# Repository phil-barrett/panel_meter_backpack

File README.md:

# Panel Meter Backpacks

Those cheap Chinese panel ammeters and voltmeters are nice additions to a project but often require some convoluted wiring. In addition, it appears that people are easily confused about the connections, the number of complaints about poor instructions and dead meters seem to indicate that.

I have been using them for a number of projects and evolved designs to make them easier to use. The AHA! moment came when I realized I could clip a PCB onto the back of the meter.  They all seem to use exactly the same plastic bezel so I could standardize the openings in the PCB.

# 5 digit USB Ammeter Ver 2.21

I was building a test setup for my [Teensy 4.1 CNC Breakout Board](https://github.com/phil-barrett/grblHAL-teensy-4.x/blob/master/README.md) and wanted to monitor USB current. The Teensy 4.1 is fairly power hungry and my board pulls even more.  I wanted to know what kind of burden the setup was placing on the USB output of my PC. In addition, I wanted to be able to characterize current draw based on various features in use.

While I had a decent DMM with fairly accurate current measuring capability, I wanted something a bit more permanant without a lot of extra wires.  The ammeter I settled on is a generic "5 digit" panel meter that sells for $6-10 USD from the usual suspect sources. I paid about $13 with tax and shipping. Characterizing it, I found it was surprisingly good, within 100 microAmps of my DMM. I designed the back pack with USB A and microUSB recepticles. It connects in-line and doesn't adversely affect USB communication. USB powers the meter itself.

My first PCB had a couple of small errors but was functional. Here is Version 2.21.
 
Here is the updated version 2.30 installed on the Panel Meter.

And, finally, mounted on a temporary panel. The light you see at the top and bottom of the meter face is light shining through from the back. It does not show when mounted in the panel of an enclosed box. 

The second iteration fixed a dumb footprint problem and used differential routing for the USB data lines. I also added silk screened information to make it clear which wires connect where. [Kicad files are here](https://github.com/phil-barrett/panel_ammeter_backpack/tree/main/design_files). However, this uses a microUSB connector I found on eBay a couple of years ago. A quick check did not show anything availble from the same source. It probably isn't available anywhere else.  I am looking for a suitable DigiKey/Mouser sourced part and will post Kicad files and an OSHPark shared project link. 

## Update

I received the V2.30 boards back from OSHPark and they work great! See the USB Ammeter V2.30 section below.

# Ammeter/Voltmeter Ver 2.50

I liked the design so much, I designed another one for those ubiquitous volt and current panel meters you see all over the place. This one uses a barrel jack and/or a screw terminal for 5-24 Volts. The meter can be powered from 5V to 30V and measure up to 100V.  I have it set up to power the meter from the measured voltage.  If you want to measure more than 30V, you will need to cut a solder jumper and use the external power pin header on the board. Output is via a screw terminal. I bought my meter from [ProtoSupplies](https://protosupplies.com/product/dual-display-0-100v-0-10a-panel-meter/). Not the cheapest but they test their meters before sending them out - something those Amazon/eBay/Aliwhatever sites clearly don't do. Protosupplies is one of my go to vendors.

Here it is mounted on the Panel Meter.

The Kicad Design files for Version 2.51 are located here and a [shared OSHPark Project is here](https://oshpark.com/shared_projects/dM8UnLfD).  You can order three boards from OSHPark for $10.95 USD. The BoM is pretty simple
  * J1, J5 - 2 position 3.5mm Screw Terminal - Common, Various Sources.
  * J2 Barrel Jack CUI Devices PJ-002A, 2.10mm ID (0.083"), 5.50mm OD (0.217"). Digikey - CP-002A-ND, Mouser - 490-PJ-002A. Many others fit this footprint.
  * J3 2.54mm 1x3 Pin Header - Common, Various Sources.
  * J4 2.54mm 1x2 Pin Header - Common, Various Sources.
  
# USB Ammeter Ver 2.30

Version 2.21 has been updated to use a more widely available USB Micro connector.  I also added a pin header and screw terminal for +5V so the backpack is now able supply power for other projects as well as USB based ones.  [OSHPark Shared Project is here](https://oshpark.com/shared_projects/VOw8OmO9).  Cost for 3 boards is $13.15 USD.   BoM is
  * J2 USB Micro A/B - Molex 47589-101. Mouser - 538-47589-1001 , DigiKey - WM14335CT-ND
  * J3 3.5mm Screw Terminal - Widely Available
  * J4 USB A Recpeticle - Amphenol ICC UE27AC5410H. Mouser - 523-UE27-AC54-100, DigiKey - UE27AC5410H-ND
  ** Update - new Amphenol Mouser Number: 649-87520-0012BLF. Same pinout.
  * JP1, JP2 1x2 2.54mm pin headers - Widely Available.

# Panel Meter Cutout

These panel meters all seem to share the same plastic bezel design.  To mount them in a panel you need to cut out a rectangle 45.5 mm by 26 mm.  (1 13/16" X 1 1/32")

The panel should be at least 1.5mm (1/16") thick but not more than 3mm (1/8"). For thicker panel material, you should make the opening a bit taller (26.5 mm or more)

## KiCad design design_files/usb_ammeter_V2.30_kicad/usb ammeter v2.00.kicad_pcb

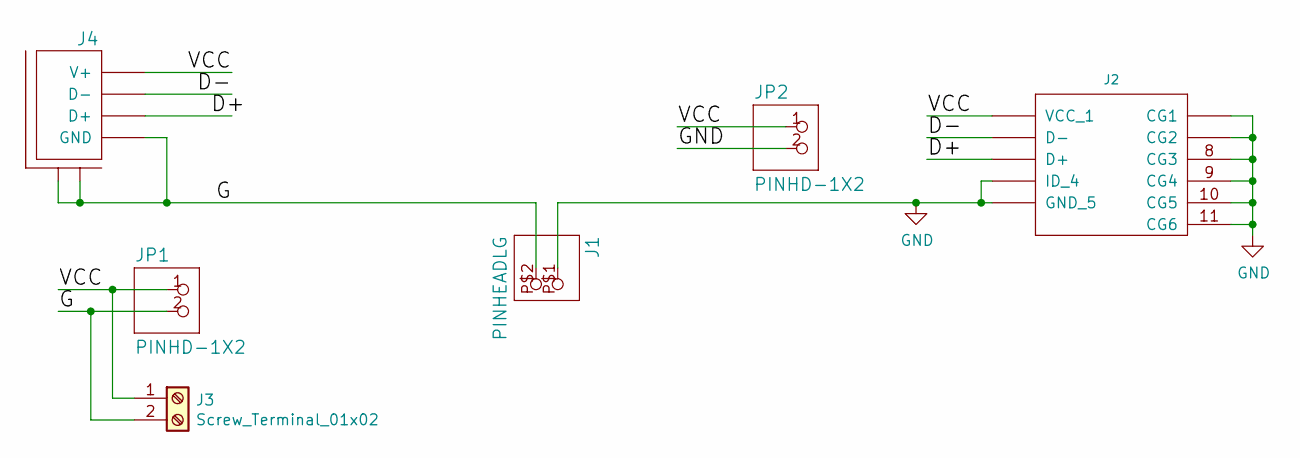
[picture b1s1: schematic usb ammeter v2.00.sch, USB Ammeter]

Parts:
J1: PINHEADLG; LG-2-PIN
J2: usb-micro-molex-sd-47589-101; molex-47589-101-microUSB-AB
J3: Screw_Terminal_01x02; T35-2
J4: USB-AMPH-UE27-AC; USBAMPH-UE27AC5410H; digikey UE27AC5410H
JP1, JP2: PINHD-1X2; 1X02

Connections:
/D+: J2.3 (D+), J4.D+
/D-: J2.2 (D-), J4.D-
/G: J1.P$2 (2), J3.2, J4.G (GND), J4.G1 (M1), J4.G2 (M2), JP1.2
/VCC: J2.1 (VCC_1), J3.1, J4.VCC (V+), JP1.1, JP2.1
GND: J1.P$1 (1), J2.4 (ID_4), J2.5 (GND_5), J2.6 (CG1), J2.7 (CG2), J2.8 (CG3), J2.9 (CG4), J2.10 (CG5), J2.11 (CG6), JP2.2

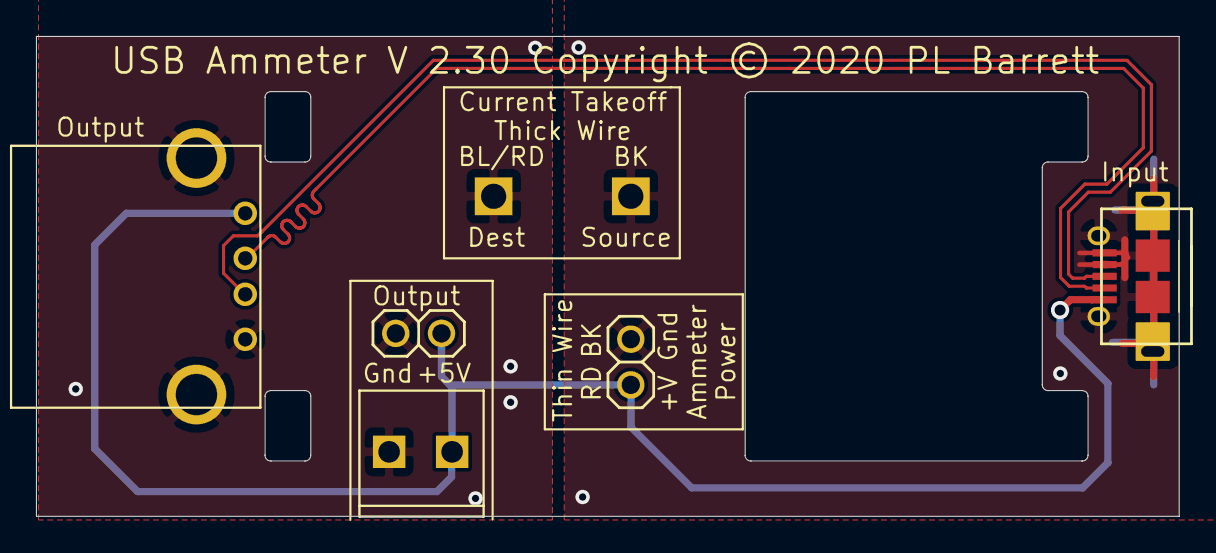
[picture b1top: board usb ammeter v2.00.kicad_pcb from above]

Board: 2 copper layers, 63.5 x 26.7 mm, 6 parts (0 on the bottom side), 5 nets.

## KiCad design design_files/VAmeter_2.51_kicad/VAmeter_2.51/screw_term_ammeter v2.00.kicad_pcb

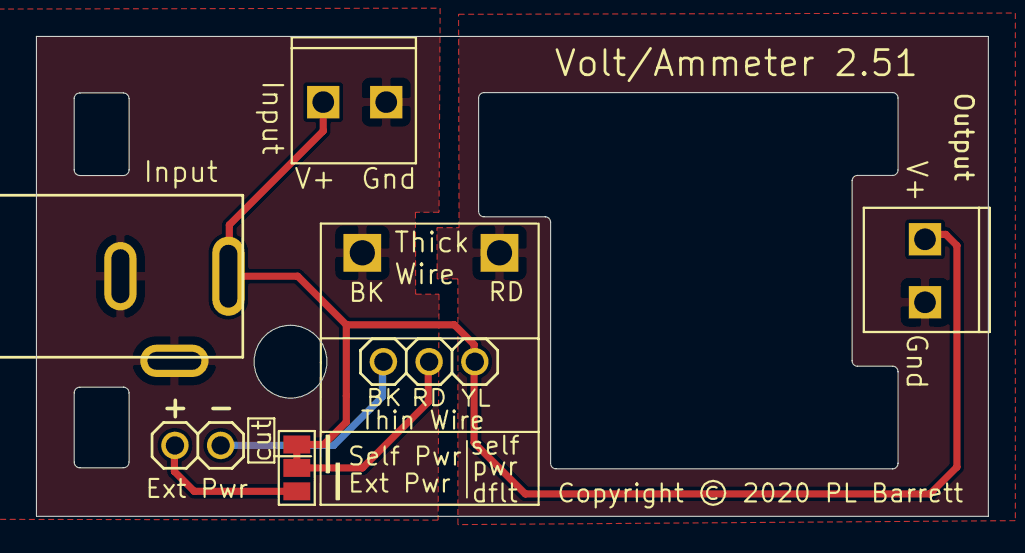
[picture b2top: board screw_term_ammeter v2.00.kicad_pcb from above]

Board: 2 copper layers, 52.9 x 26.7 mm, 7 parts (0 on the bottom side), 5 nets.

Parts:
J1, J5: Screw_Terminal_01x02; T35-2
J2: Barrel_Jack; DC_Conn_PJ-002A
J3: Conn_01x03; 1X03
J4: Conn_01x02; 1X02
J6: Conn_01x02; LG-2-PIN
JP1: JUMPER-SMT_3_NO_NO-SILK; SolderJumper-3_P1.3mm_Open_Pad1.0x1.5mm

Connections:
/G: J1.2, J2.2, J2.3, J6.2
/GND: J5.2, J6.1
/VCC: J1.1, J2.1, J3.1, J3.2, J5.1, JP1.2, JP1.3
unnamed: J3.3, J4.2
unnamed: J4.1, JP1.1

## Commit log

2020-12-13 Create README.md
    Initial Commit of ReadMe.
2020-12-13 Initial photo commits
2020-12-27 Update part number.

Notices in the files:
design_files/VAmeter_2.51_kicad/VAmeter_2.51/screw_term_ammeter v2.00.kicad_pcb:
Copyright © 2020 PL Barrett
design_files/usb_ammeter_V2.30_kicad/usb ammeter v2.00.kicad_pcb:
USB Ammeter V 2.30 Copyright © 2020 PL Barrett
